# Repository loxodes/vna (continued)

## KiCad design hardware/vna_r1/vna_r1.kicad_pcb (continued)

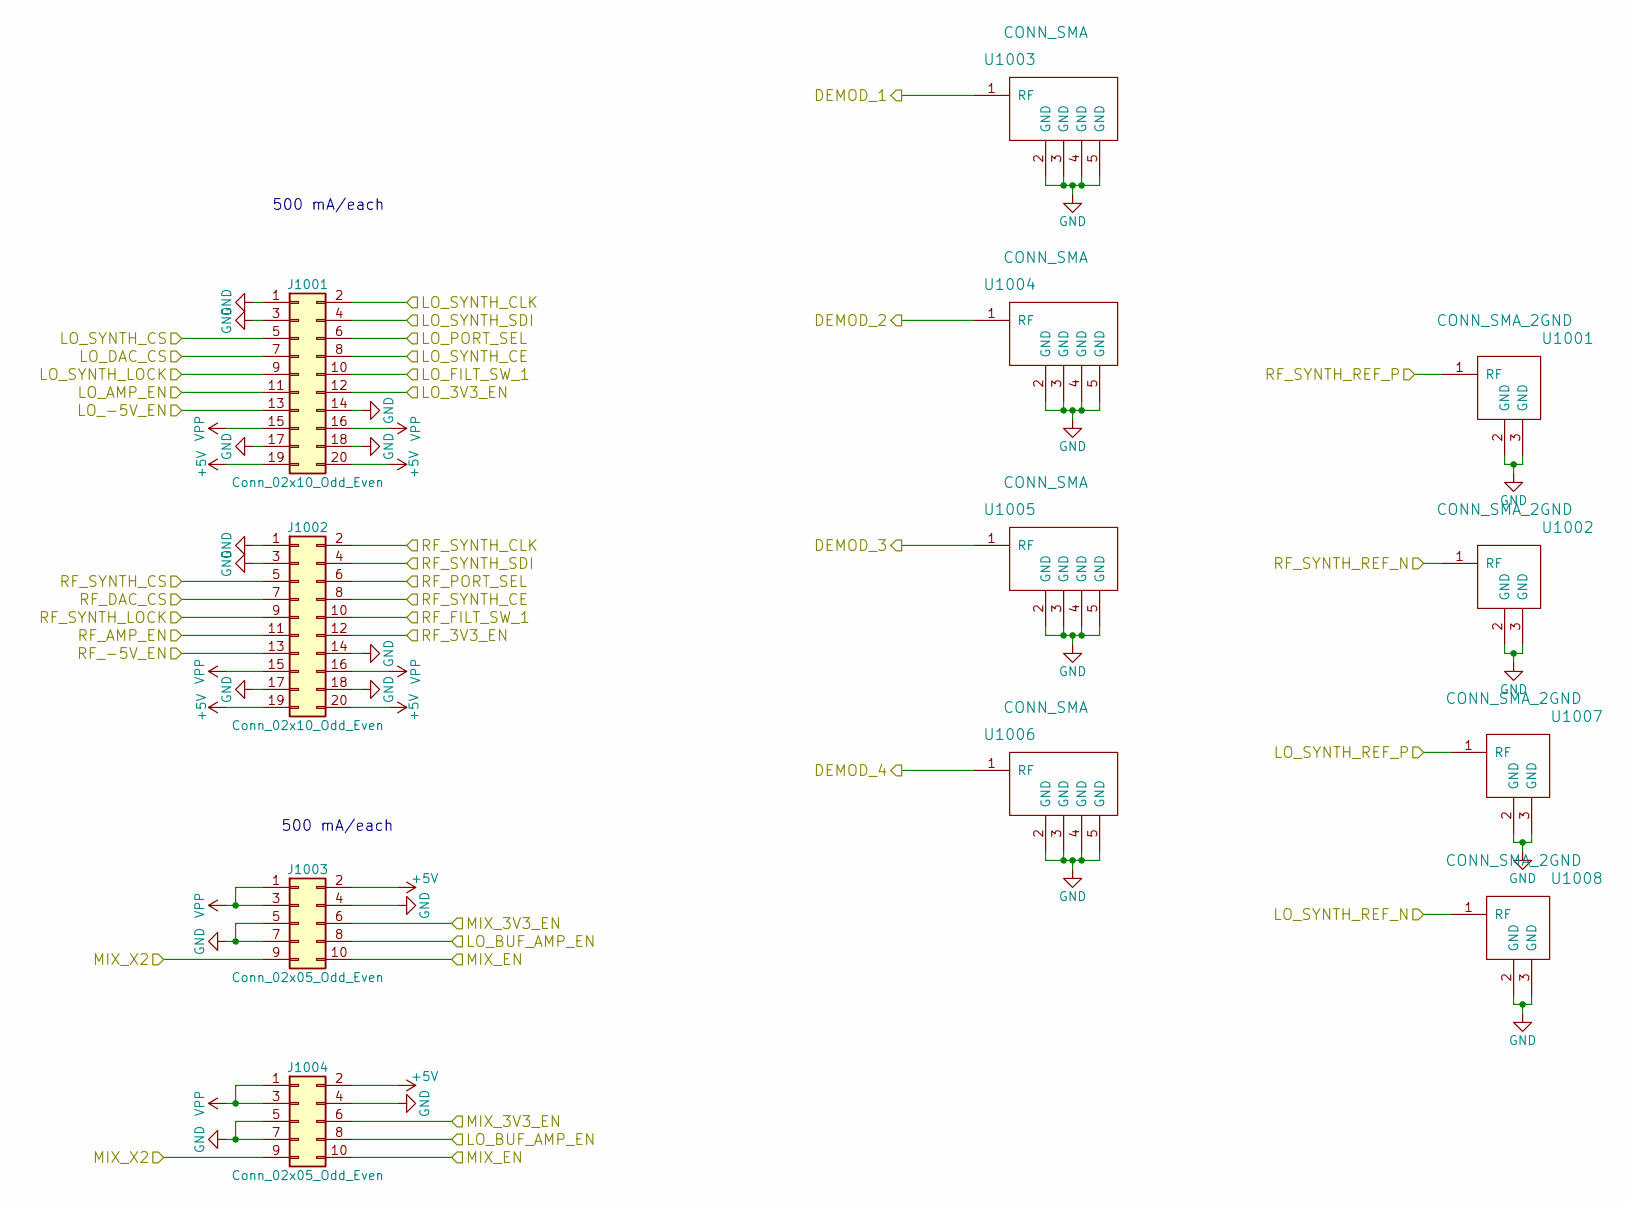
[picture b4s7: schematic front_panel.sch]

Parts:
J1001, J1002: Conn_02x10_Odd_Even; IDC_Header_Straight_20pins
J1003, J1004: Conn_02x05_Odd_Even; IDC_Header_Straight_10pins
U1001, U1002, U1007, U1008: CONN_SMA_2GND; 734120110_ufl_umc
U1003, U1004, U1005, U1006: CONN_SMA; 732511150_sma_thin

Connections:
+5V: J1001.19, J1001.20, J1002.19, J1002.20, J1003.2, J1004.2; also elsewhere on the board
/3V3_DEMOD_EXT_EN: J1003.6, J1004.6; also elsewhere on the board
/LO_3V3_EN: J1001.12; also elsewhere on the board
/LO_-5V_EN: J1001.13; also elsewhere on the board
/LO_AMP_EN: J1001.11; also elsewhere on the board
/LO_BUF_AMP_EN: J1003.8, J1004.8; also elsewhere on the board
/LO_DAC_CS: J1001.7; also elsewhere on the board
/LO_PORT_SEL: J1001.6; also elsewhere on the board
/LO_SPI_CLK: J1001.2; also elsewhere on the board
/LO_SPI_SDI: J1001.4; also elsewhere on the board
/LO_SYNTH_CE: J1001.8; also elsewhere on the board
/LO_SYNTH_CS: J1001.5; also elsewhere on the board
/LO_SYNTH_LOCK: J1001.9; also elsewhere on the board
/MIX_EN: J1003.10, J1004.10; also elsewhere on the board
/MIX_X2: J1003.9, J1004.9; also elsewhere on the board
/RF_3V3_EN: J1002.12; also elsewhere on the board
/RF_-5V_EN: J1002.13; also elsewhere on the board
/RF_AMP_EN: J1002.11; also elsewhere on the board
/RF_DAC_CS: J1002.7; also elsewhere on the board
/RF_FILT_SW_1: J1002.10; also elsewhere on the board
/RF_FILT_SW_2: J1001.10; also elsewhere on the board
/RF_PORT_SEL: J1002.6; also elsewhere on the board
/RF_SPI_CLK: J1002.2; also elsewhere on the board
/RF_SPI_SDI: J1002.4; also elsewhere on the board
/RF_SYNTH_CE: J1002.8; also elsewhere on the board
/RF_SYNTH_CS: J1002.5; also elsewhere on the board
/RF_SYNTH_LOCK: J1002.9; also elsewhere on the board
/SYNTH_REF_AN: U1008.1 (RF); also elsewhere on the board
/SYNTH_REF_AP: U1007.1 (RF); also elsewhere on the board
/SYNTH_REF_BN: U1002.1 (RF); also elsewhere on the board
/SYNTH_REF_BP: U1001.1 (RF); also elsewhere on the board
/front_panel/DEMOD_1: U1003.1 (RF); also elsewhere on the board
/front_panel/DEMOD_2: U1004.1 (RF); also elsewhere on the board
/front_panel/DEMOD_3: U1005.1 (RF); also elsewhere on the board
/front_panel/DEMOD_4: U1006.1 (RF); also elsewhere on the board
GND: J1001.1, J1001.3, J1001.14, J1001.17, J1001.18, J1002.1, J1002.3, J1002.14, J1002.17, J1002.18, J1003.4, J1003.5, J1003.7, J1004.4, J1004.5, J1004.7, U1001.2 (GND), U1001.3 (GND), U1002.2 (GND), U1002.3 (GND), U1003.2 (GND), U1003.3 (GND), U1003.4 (GND), U1003.5 (GND), U1004.2 (GND), U1004.3 (GND), U1004.4 (GND), U1004.5 (GND), U1005.2 (GND), U1005.3 (GND), U1005.4 (GND), U1005.5 (GND), U1006.2 (GND), U1006.3 (GND), U1006.4 (GND), U1006.5 (GND), U1007.2 (GND), U1007.3 (GND), U1008.2 (GND), U1008.3 (GND); also elsewhere on the board
VPP: J1001.15, J1001.16, J1002.15, J1002.16, J1003.1, J1003.3, J1004.1, J1004.3; also elsewhere on the board

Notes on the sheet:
500 mA/each

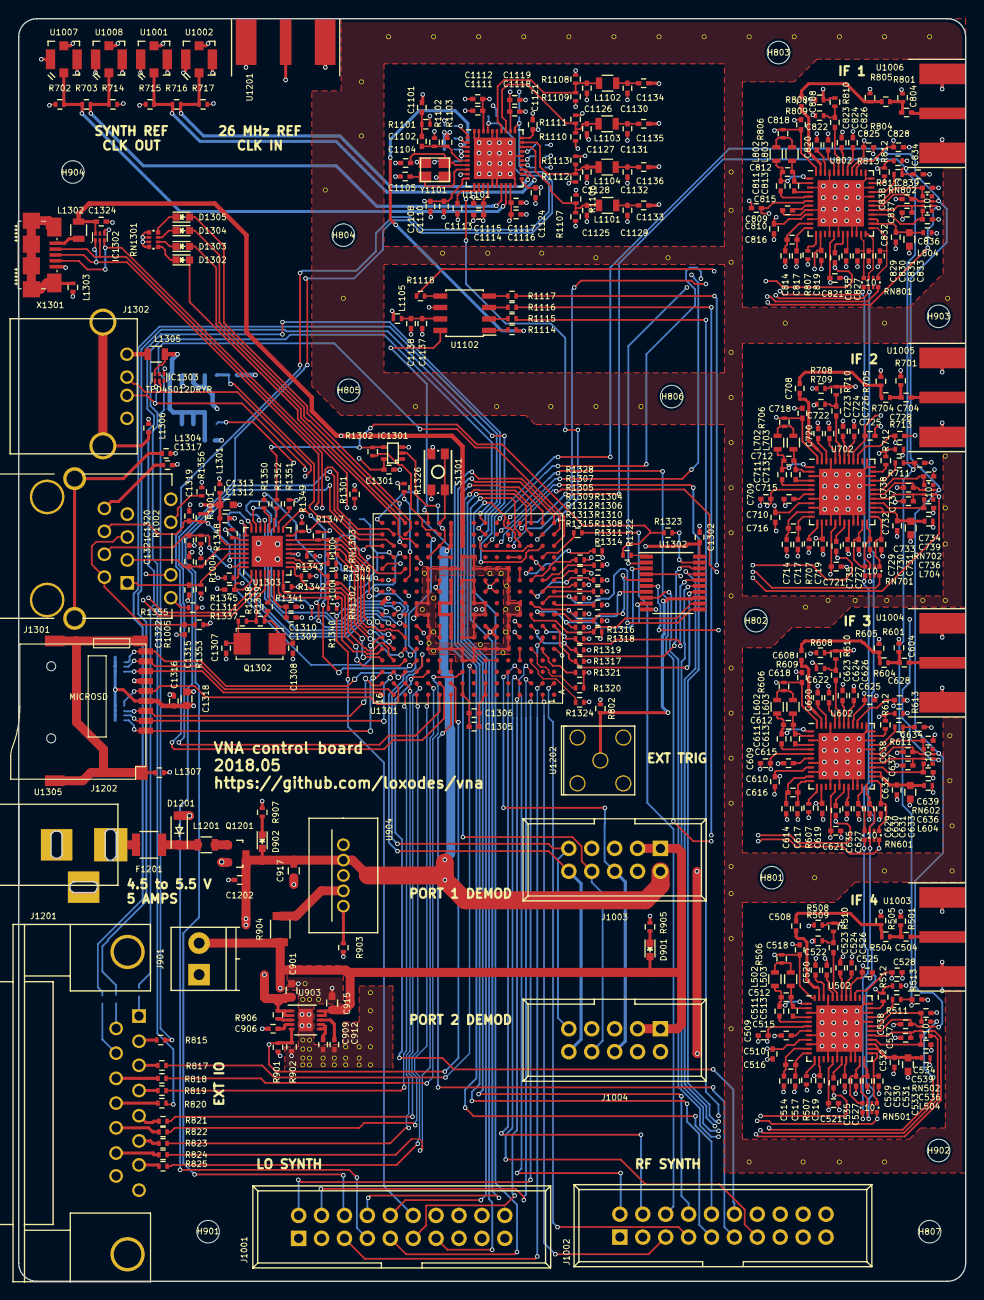
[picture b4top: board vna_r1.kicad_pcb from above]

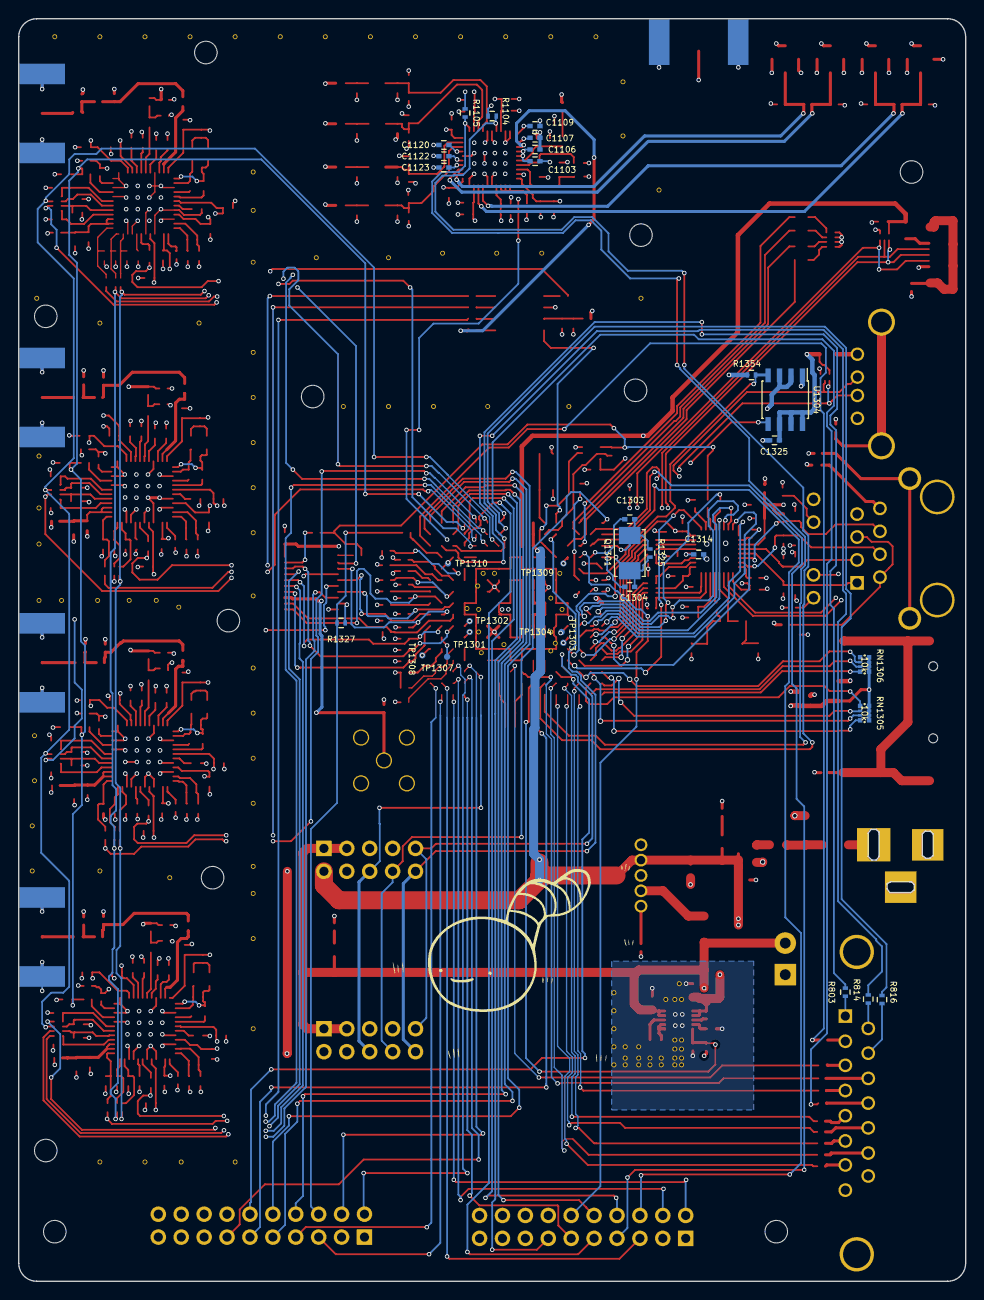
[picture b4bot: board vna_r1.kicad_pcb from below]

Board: 4 copper layers, 105.0 x 140.0 mm, 447 parts (31 on the bottom side), 375 nets.

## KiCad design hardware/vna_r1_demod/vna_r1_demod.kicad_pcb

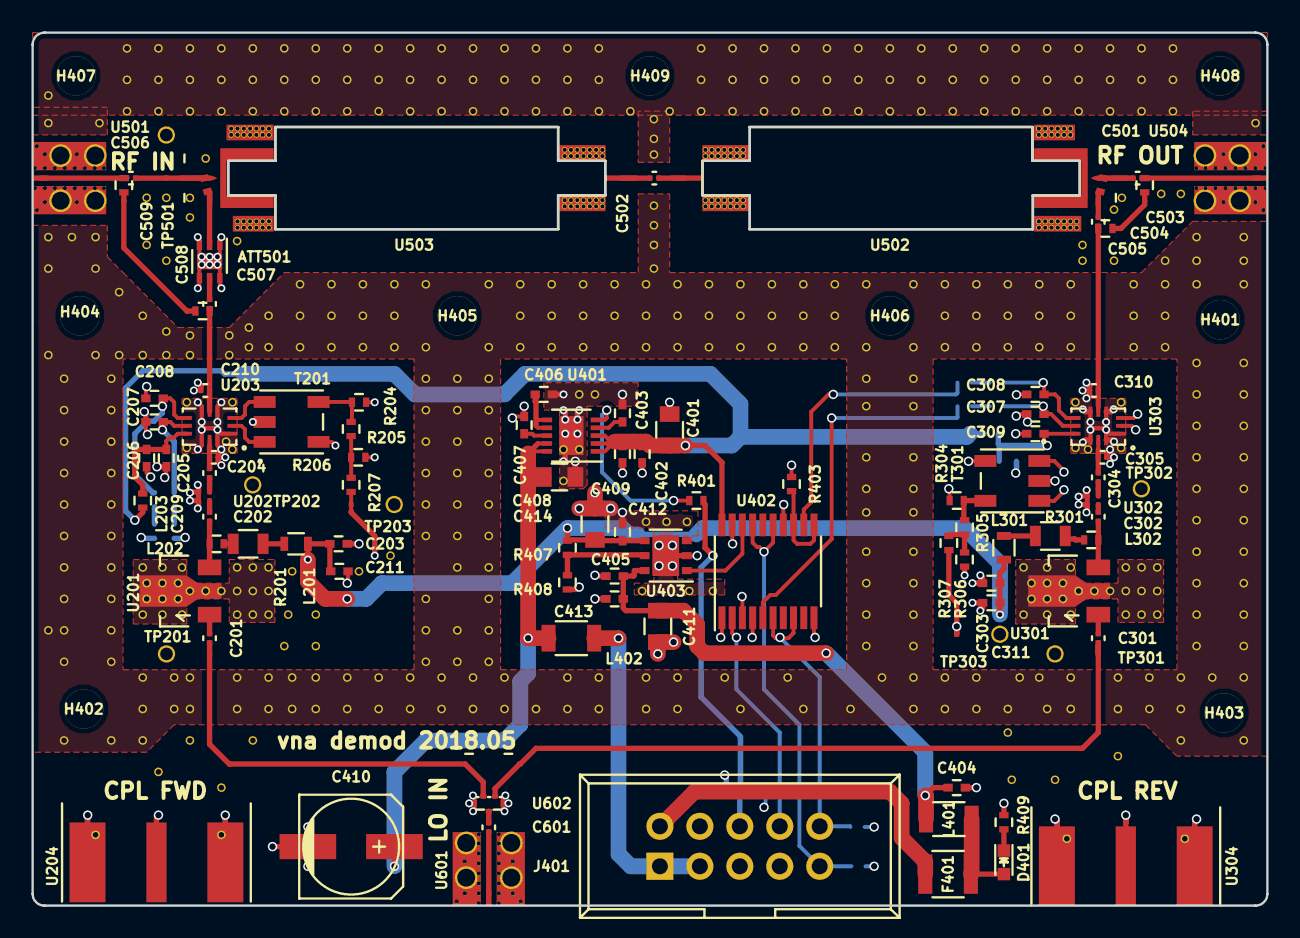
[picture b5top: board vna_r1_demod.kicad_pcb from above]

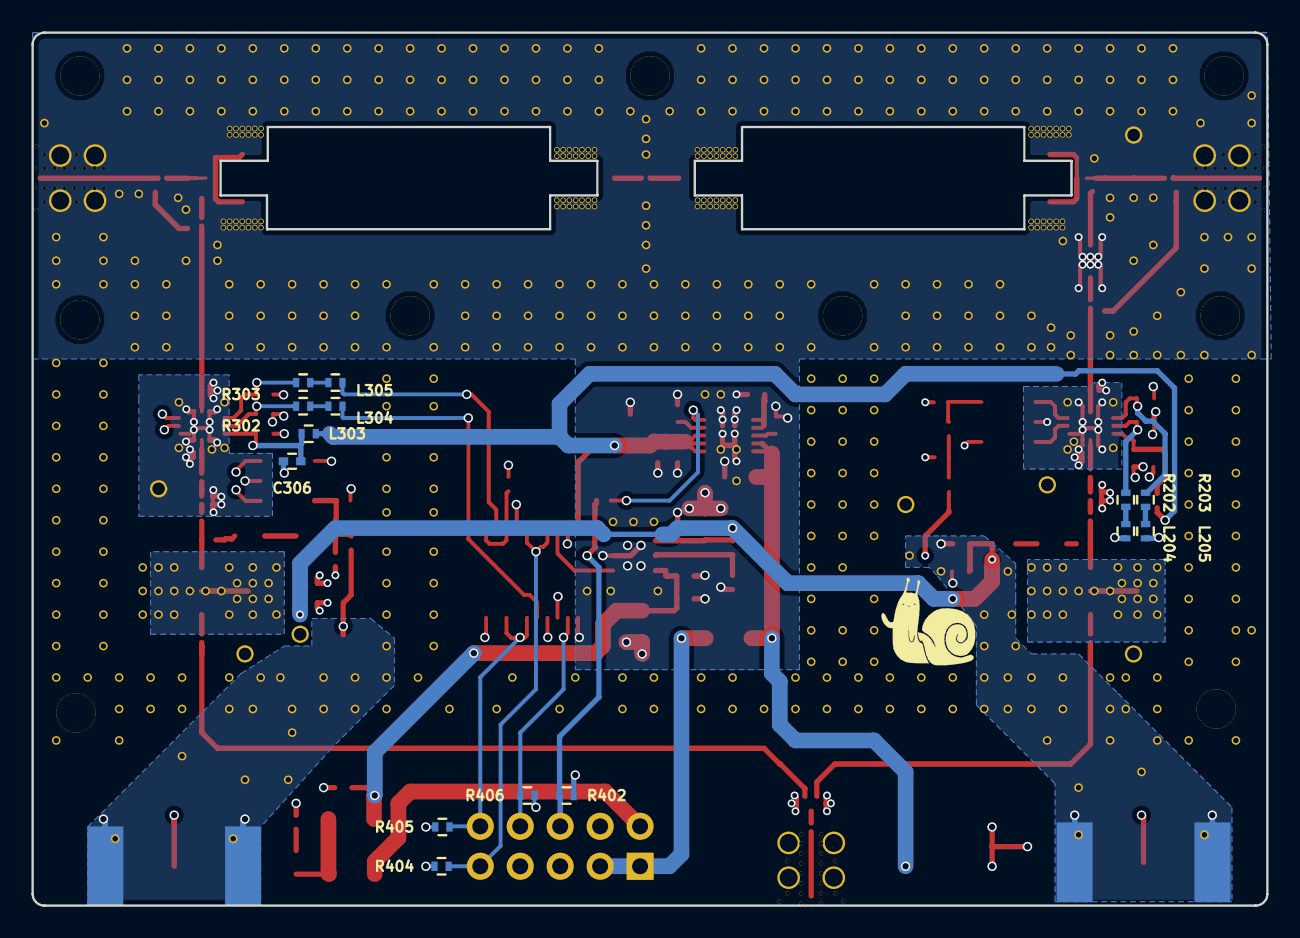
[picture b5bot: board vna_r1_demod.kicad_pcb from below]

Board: 4 copper layers, 78.5 x 55.5 mm, 120 parts (14 on the bottom side), 75 nets.

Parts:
ATT501: HMC657LP2E; DFN-6-1EP_2x2mm_Pitch0.65mm
C201, C202, C204, C205, C301, C302, C304, C305, C505, C507, C601: C_Small; C_0201
C203, C206, C207, C208, C209, C211, C303, C306, C307, C308, C309, C311, C409: C_Small; C_0402
C210, C310: DNP; C_0201
C401, C408: 10 uF; C_0805
C402, C403, C404, C406, C407, C413: 1 uF; C_0402
C405, C412: 100 nF; C_0402
C410: 4.7 uF; c_elec_6.3x5.8
C411, C414: 4.7 uF; C_0805
C501, C502, C506: 10 pF; C_0201
C503, C504, C508, C509: DNP; R_0402
D401: LED; LED_0603
F401: Polyfuse_Small; R_1210
H401, H402, H403, H404, H405, H406, H407, H408, H409: MOUNTING_HOLE; MountingHole_2-5mm
J401: Conn_02x05_Odd_Even; IDC_Header_Straight_10pins
L201, L301: L_Small; R_0603
L202, L203, L204, L205, L302, L303, L304, L305: L_Small; R_0402
L401, L402: L_Small; R_1206
R201, R301: 13; R_0805
R202, R203, R204, R205, R206, R207, R302, R303, R304, R305, R306, R307: R_Small; R_0402
R401: 100; R_0402
R402, R403, R404, R405, R406, R409: 10k; R_0402
R407: 47k; R_0402
R408: 12k; R_0402
T201, T301: Transformer_SP_1S; 5LEAD_BALUN_4p83mm_3p3mm
TP201, TP202, TP203, TP301, TP302, TP303, TP501: TP_RF; TP-P20B
U201, U301: SKY65013-70LF; SOT89-3_Housing
U202, U302: PAT0510S-C-XDB-T10; PAT0510S
U203, U303: LTC5548; QFN_12_3mm2mm
U204, U304: CONN_SMA; 732511150_sma_thin
U401: ADP7158; DFN-10-1EP_3x3mm_Pitch0.5mm
U402: 74HC244; TSSOP-20_4.4x6.5mm_Pitch0.65mm
U403: LD39100; DFN-6-1EP_3x3mm_Pitch0.95mm
U501, U504, U601: CONN_SMA_2GND; SMA_901-10512_6p7MIL_FR408_CPW_LAUNCH
U502: resistive_bridge; resistive_bridge_osh_fr408_ustrip_mirrored
U503: resistive_bridge; resistive_bridge_osh_fr408_ustrip
U602: PWR_SPLITTER; PS1608

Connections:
+3V3: C401.1, C402.1, C409.1, L203.2, L303.2, U401.1, U401.2, U401.3, U402.20
+5V: C404.1, C405.1, C411.1, C413.1, L401.2, U403.6
/LO_AMP_A: C203.2, C211.2, C303.2, C311.2, C412.1, C414.1, L201.2, L301.2, R407.1, U403.4
/MIX_EN_A: L205.2, U402.14
/MIX_EN_B: L305.2, U402.12
/X2_EN_A: L204.2, U402.3
/X2_EN_B: L304.2, U402.5
/couplers/CPL_FWD: C210.2, C507.1, C508.2, U203.5
/couplers/CPL_REV: C310.2, C504.2, C505.1, U303.5
/lo_split/LO_A: C201.2, TP201.1, U602.3
/lo_split/LO_B: C301.2, TP301.1, U602.2
/power_conn/EXT_3V3_EN: J401.6, R401.2, R402.2
/power_conn/EXT_LO_AMP_EN: J401.8, R406.2, U402.2
/power_conn/EXT_MIX_EN: J401.10, R405.2, U402.6, U402.8
/power_conn/EXT_X2_EN: J401.9, R404.2, U402.15, U402.17
/power_conn/LO_AMP_EN: U402.18, U403.1
GND: ATT501.1, ATT501.3, ATT501.4, ATT501.6, ATT501.7, C203.1, C205.2, C206.2, C207.1, C208.1, C209.2, C210.1, C211.1, C303.1, C305.2, C306.2, C307.1, C308.1, C309.2, C310.1, C311.1, C401.2, C402.2, C403.2, C404.2, C405.2, C406.2, C407.2, C408.2, C409.2, C410.2, C411.2, C412.2, C413.2, C414.2, J401.4, J401.5, J401.7, R204.2, R206.2, R304.2, R306.2, R402.1, R403.1, R404.1, R405.1, R406.1, R408.2, R409.1, T201.2, T201.5, T301.2, T301.5, TP201.2, TP202.2, TP203.2, TP301.2, TP302.2, TP303.2, TP501.2, U201.2, U202.3, U202.4, U203.1, U203.4, U203.6, U203.10, U203.12, U203.13, U204.2, U204.3, U204.4, U204.5, U301.2, U302.3, U302.4, U303.1, U303.4, U303.6, U303.10, U303.12, U303.13, U304.2, U304.3, U304.4, U304.5, U401.11, U402.1, U402.4, U402.10, U402.19, U403.2, U403.7, U501.2, U501.3, U502.4, U503.4, U504.2, U504.3, U601.2, U601.3, U602.4
unnamed: ATT501.2, U503.3
unnamed: ATT501.5, C507.2
unnamed: C201.1, U201.1
unnamed: C202.1, U202.2
unnamed: C202.2, L202.1, U201.3
unnamed: C204.1, TP202.1, U202.1
unnamed: C204.2, C205.1, U203.11
unnamed: C206.1, C209.1, L203.1, U203.9
unnamed: C207.2, R202.1, U203.8
unnamed: C208.2, R203.1, U203.7
unnamed: C301.1, U301.1
unnamed: C302.1, U302.2
unnamed: C302.2, L302.1, U301.3
unnamed: C304.1, TP302.1, U302.1
unnamed: C304.2, C305.1, U303.11
unnamed: C306.1, C309.1, L303.1, U303.9
unnamed: C307.2, R302.1, U303.8
unnamed: C308.2, R303.1, U303.7
unnamed: C403.1, U401.4
unnamed: C406.1, U401.6, U401.7
unnamed: C407.1, U401.8
unnamed: C501.1, U502.2
unnamed: C501.2, C503.2, U504.1
unnamed: C502.1, U503.1
unnamed: C502.2, U502.1
unnamed: C503.1, C504.1
unnamed: C505.2, U502.3
unnamed: C506.1, C509.2, U501.1
unnamed: C506.2, TP501.1, U503.2
unnamed: C508.1, C509.1
unnamed: C601.1, U602.1
unnamed: C601.2, U601.1
unnamed: D401.1, R409.2
unnamed: D401.2, F401.1, L401.1
unnamed: F401.2, J401.2
unnamed: J401.1, J401.3, L402.2
unnamed: L201.1, R201.2
unnamed: L202.2, R201.1
unnamed: L204.1, R202.2
unnamed: L205.1, R203.2
unnamed: L301.1, R301.2
unnamed: L302.2, R301.1
unnamed: L304.1, R302.2
unnamed: L305.1, R303.2
unnamed: R204.1, R205.1, T201.4
unnamed: R205.2, R206.1, R207.1
unnamed: R207.2, TP203.1, U204.1
unnamed: R304.1, R305.1, T301.4
unnamed: R305.2, R306.1, R307.1
unnamed: R307.2, TP303.1, U304.1
unnamed: R401.1, U401.5
unnamed: R403.2, U402.11, U402.13
unnamed: R407.2, R408.1, U403.5
unnamed: T201.1, U203.2
unnamed: T201.3, U203.3
unnamed: T301.1, U303.2
unnamed: T301.3, U303.3
VPP: C408.1, C410.1, L402.1, U401.9, U401.10

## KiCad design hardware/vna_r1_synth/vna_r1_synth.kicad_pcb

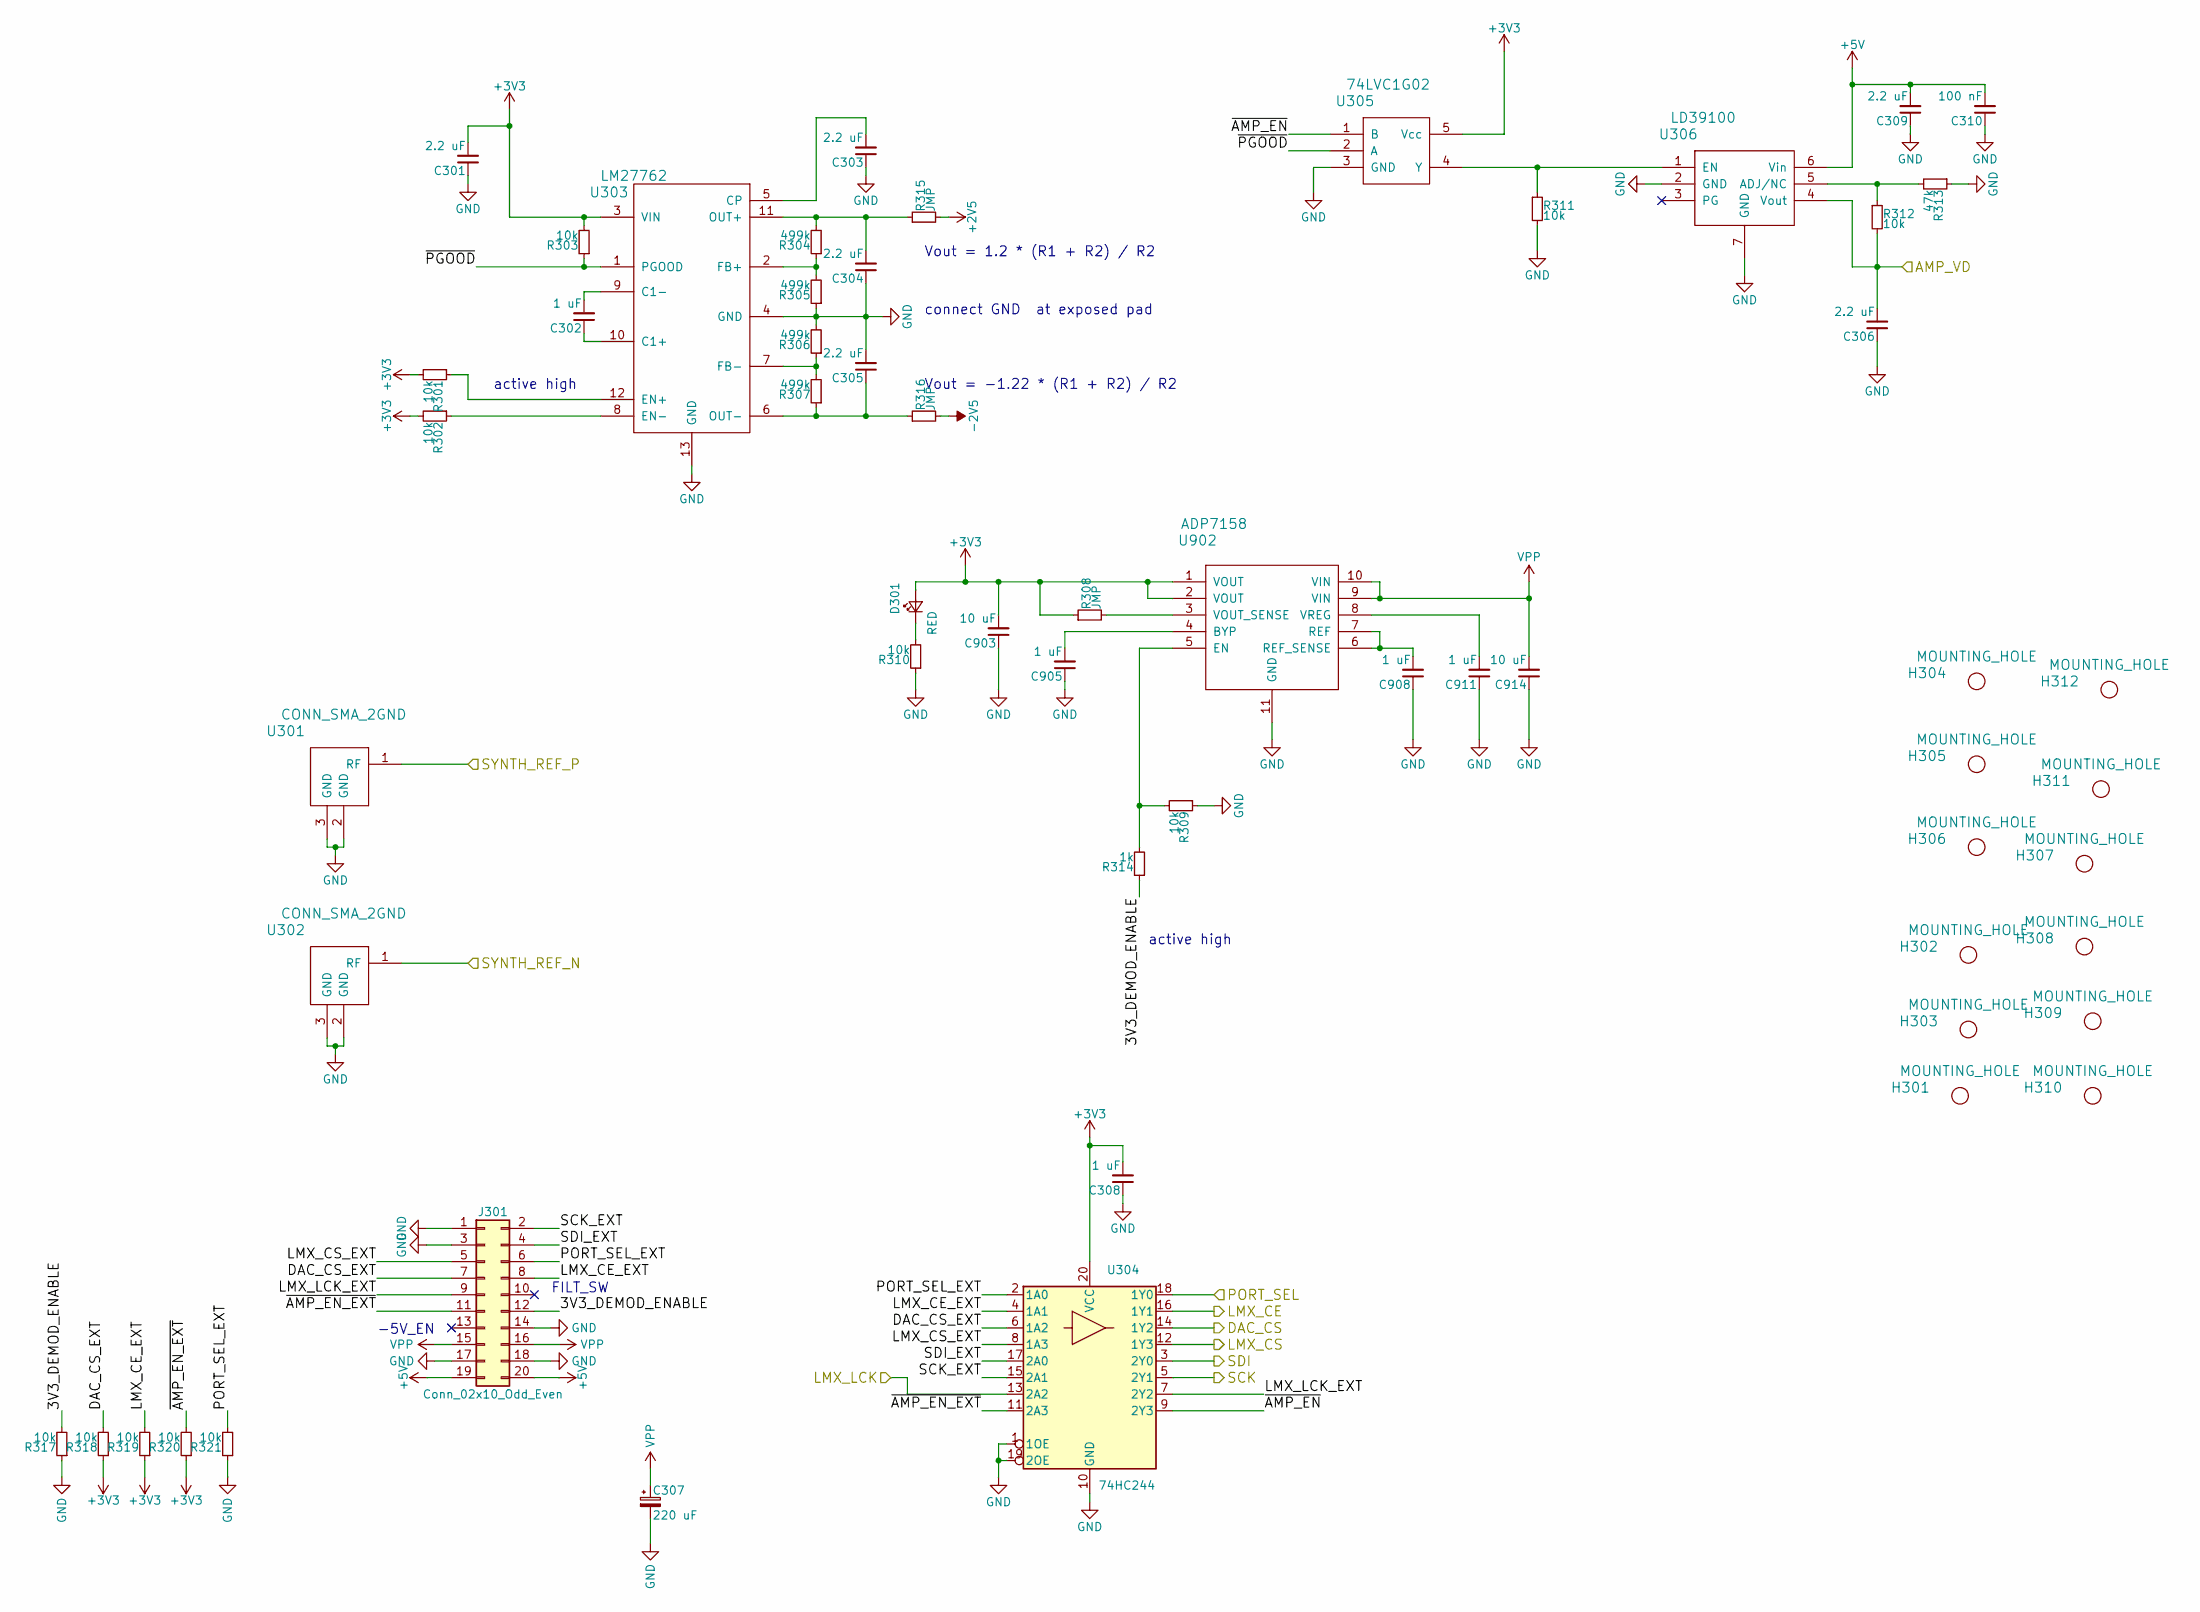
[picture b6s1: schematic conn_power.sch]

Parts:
C301, C303, C304, C305, C309: 2.2 uF; C_0603
C302, C308, C905, C908, C911: 1 uF; C_0402
C306: 2.2 uF; C_0402
C307: 220 uF; c_elec_6.3x5.8
C310: 100 nF; C_0402
C903, C914: 10 uF; C_0603
D301: RED; LED_0603
H301, H302, H303, H304, H305, H306, H307, H308, H309, H310, H311, H312: MOUNTING_HOLE; MountingHole_2-5mm
J301: Conn_02x10_Odd_Even; IDC_Header_Straight_20pins
R301, R302, R303, R309, R310, R311, R312, R317, R318, R319, R320, R321: 10k; R_0402
R304, R305, R306, R307: 499k; R_0402
R308, R315, R316: JMP; R_0402
R313: 47k; R_0402
R314: 1k; R_0402
U301, U302: CONN_SMA_2GND; 734120110_ufl_umc
U303: LM27762; WSON-12-1EP_3x2mm_Pitch0.5mm
U304: 74HC244; TSSOP-20_4.4x6.5mm_Pitch0.65mm
U305: 74LVC1G02; SOT-23-5
U306: LD39100; DFN-6-1EP_3x3mm_Pitch0.95mm
U902: ADP7158; DFN-10-1EP_3x3mm_Pitch0.5mm

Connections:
+2V5: R315.2; also elsewhere on the board
+3V3: C301.2, C308.2, C903.2, D301.2 (A), R301.2, R302.2, R303.2, R308.1, R318.1, R319.1, R320.1, U303.3 (VIN), U304.20 (VCC), U305.5 (Vcc), U902.1 (VOUT), U902.2 (VOUT); also elsewhere on the board
+5V: C309.2, C310.2, J301.19, J301.20, U306.6 (Vin)
-2V5: R316.2; also elsewhere on the board
/AMP_VD: C306.2, R312.2, U306.4 (Vout); also elsewhere on the board
/DAC_CS: U304.14 (1Y2); also elsewhere on the board
/PORT_SEL: U304.18 (1Y0); also elsewhere on the board
/SPI_SCK: U304.5 (2Y1); also elsewhere on the board
/SPI_SDI: U304.3 (2Y0); also elsewhere on the board
/conn_power/3V3_DEMOD_ENABLE: J301.12, R314.1, R317.2
/conn_power/DAC_CS_EXT: J301.7, R318.2, U304.6 (1A2)
/conn_power/LMX_CE: U304.16 (1Y1); also elsewhere on the board
/conn_power/LMX_CE_EXT: J301.8, R319.2, U304.4 (1A1)
/conn_power/LMX_CS: U304.12 (1Y3); also elsewhere on the board
/conn_power/LMX_CS_EXT: J301.5, U304.8 (1A3)
/conn_power/LMX_LCK: U304.13 (2A2); also elsewhere on the board
/conn_power/LMX_LCK_EXT: J301.9, U304.7 (2Y2)
/conn_power/PORT_SEL_EXT: J301.6, R321.2, U304.2 (1A0)
/conn_power/SCK_EXT: J301.2, U304.15 (2A1)
/conn_power/SDI_EXT: J301.4, U304.17 (2A0)
/conn_power/SYNTH_REF_N: U302.1 (RF); also elsewhere on the board
/conn_power/SYNTH_REF_P: U301.1 (RF); also elsewhere on the board
/conn_power/~AMP_EN: U304.9 (2Y3), U305.1 (B)
/conn_power/~AMP_EN_EXT: J301.11, R320.2, U304.11 (2A3)
/conn_power/~PGOOD: R303.1, U303.1 (PGOOD), U305.2 (A)
GND: C301.1, C303.1, C304.1, C305.2, C306.1, C307.2, C308.1, C309.1, C310.1, C903.1, C905.1, C908.1, C911.1, C914.1, J301.1, J301.3, J301.14, J301.17, J301.18, R305.1, R306.2, R309.1, R310.1, R311.2, R313.1, R317.1, R321.1, U301.2 (GND), U301.3 (GND), U302.2 (GND), U302.3 (GND), U303.4 (GND), U303.13 (GND), U304.1 (1OE), U304.10 (GND), U304.19 (2OE), U305.3 (GND), U306.2 (GND), U306.7 (GND), U902.11 (GND); also elsewhere on the board
unnamed: C302.1, U303.10 (C1+)
unnamed: C302.2, U303.9 (C1-)
unnamed: C303.2, U303.5 (CP)
unnamed: C304.2, R304.2, R315.1, U303.11 (OUT+)
unnamed: C305.1, R307.1, R316.1, U303.6 (OUT-)
unnamed: C905.2, U902.4 (BYP)
unnamed: C908.2, U902.6 (REF_SENSE), U902.7 (REF)
unnamed: C911.2, U902.8 (VREG)
unnamed: D301.1 (K), R310.2
unnamed: R301.1, U303.12 (EN+)
unnamed: R302.1, U303.8 (EN-)
unnamed: R304.1, R305.2, U303.2 (FB+)
unnamed: R306.1, R307.2, U303.7 (FB-)
unnamed: R308.2, U902.3 (VOUT_SENSE)
unnamed: R309.2, R314.2, U902.5 (EN)
unnamed: R311.1, U305.4 (Y), U306.1 (EN)
unnamed: R312.1, R313.2, U306.5 (ADJ/NC)
VPP: C307.1, C914.2, J301.15, J301.16, U902.9 (VIN), U902.10 (VIN)

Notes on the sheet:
active high
Vout = 1.2 * (R1 + R2) / R2
Vout = -1.22 * (R1 + R2) / R2
connect GND at exposed pad
-5V_EN
FILT_SW

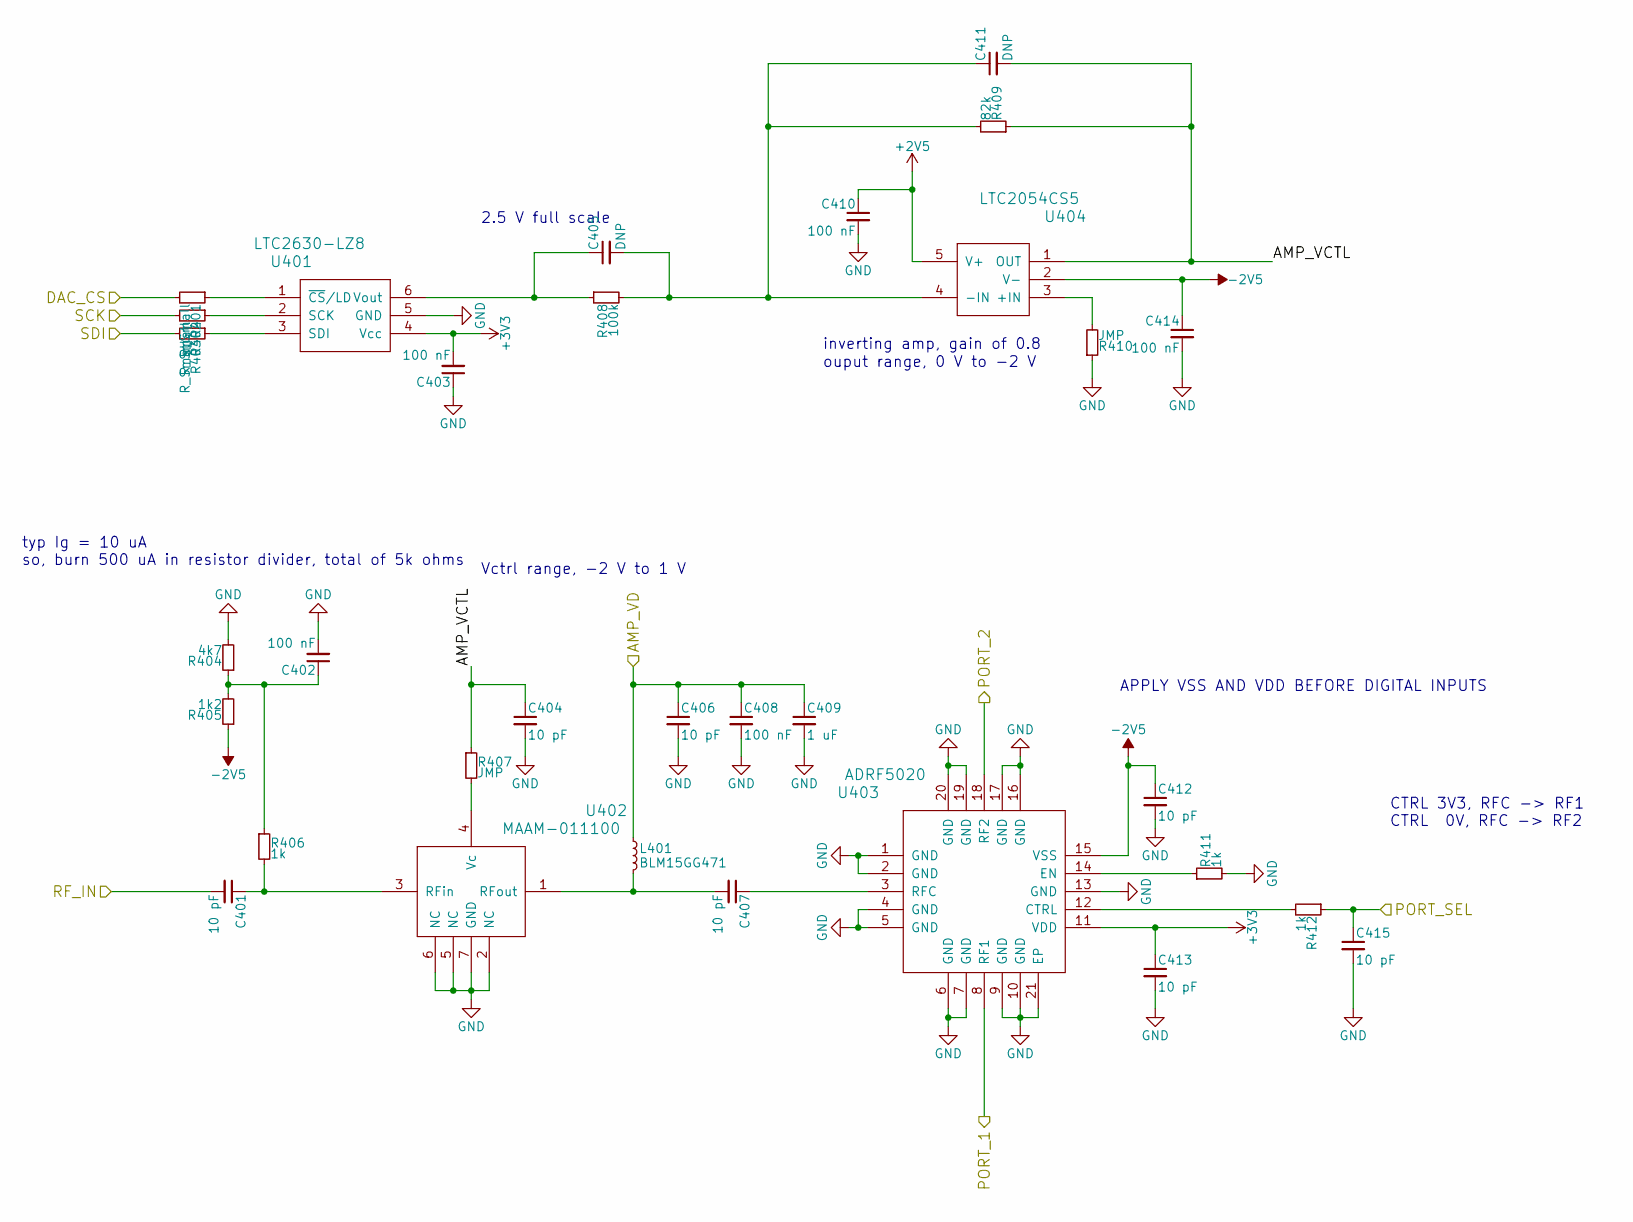
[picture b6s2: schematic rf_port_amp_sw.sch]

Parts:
C401, C407: 10 pF; C_0201
C402, C403, C408, C410, C414: 100 nF; C_0402
C404, C406, C412, C413, C415: 10 pF; C_0402
C405, C411: DNP; C_0402
C409: 1 uF; C_0402
L401: BLM15GG471; R_0402
R401, R402, R403: R_Small; R_0402
R404: 4k7; R_0402
R405: 1k2; R_0402
R406, R411, R412: 1k; R_0402
R407, R410: JMP; R_0402
R408: 100k; R_0402
R409: 82k; R_0402
U401: LTC2630-LZ8; SC-70-6
U402: MAAM-011100; TDFN6
U403: ADRF5020; ADRF5020BCCZN
U404: LTC2054CS5; SOT-23-5

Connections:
+2V5: C410.1, U404.5 (V+); also elsewhere on the board
+3V3: C403.2, C413.1, U401.4 (Vcc), U403.11 (VDD); also elsewhere on the board
-2V5: C412.1, C414.1, R405.1, U403.15 (VSS), U404.2 (V-); also elsewhere on the board
/AMP_VD: C406.1, C408.1, C409.1, L401.1; also elsewhere on the board
/DAC_CS: R401.2; also elsewhere on the board
/PORT_SEL: C415.1, R412.1; also elsewhere on the board
/RF_PORT: C401.2; also elsewhere on the board
/SPI_SCK: R402.2; also elsewhere on the board
/SPI_SDI: R403.2; also elsewhere on the board
/conn_front/PORT_1: U403.8 (RF1); also elsewhere on the board
/conn_front/PORT_2: U403.18 (RF2); also elsewhere on the board
/rf_port_amp_sw/AMP_VCTL: C404.1, C411.2, R407.1, R409.1, U404.1 (OUT)
GND: C402.2, C403.1, C404.2, C406.2, C408.2, C409.2, C410.2, C412.2, C413.2, C414.2, C415.2, R404.2, R410.1, R411.2, U401.5 (GND), U402.2 (NC), U402.5 (NC), U402.6 (NC), U402.7 (GND), U403.1 (GND), U403.2 (GND), U403.4 (GND), U403.5 (GND), U403.6 (GND), U403.7 (GND), U403.9 (GND), U403.10 (GND), U403.13 (GND), U403.16 (GND), U403.17 (GND), U403.19 (GND), U403.20 (GND), U403.21 (EP); also elsewhere on the board
unnamed: C401.1, R406.2, U402.3 (RFin)
unnamed: C402.1, R404.1, R405.2, R406.1
unnamed: C405.1, R408.1, U401.6 (Vout)
unnamed: C405.2, C411.1, R408.2, R409.2, U404.4 (-IN)
unnamed: C407.1, U403.3 (RFC)
unnamed: C407.2, L401.2, U402.1 (RFout)
unnamed: R401.1, U401.1 (~CS~/LD)
unnamed: R402.1, U401.2 (SCK)
unnamed: R403.1, U401.3 (SDI)
unnamed: R407.2, U402.4 (Vc)
unnamed: R410.2, U404.3 (+IN)
unnamed: R411.1, U403.14 (EN)
unnamed: R412.2, U403.12 (CTRL)

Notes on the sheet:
CTRL 3V3, RFC -> RF1 CTRL 0V, RFC -> RF2
APPLY VSS AND VDD BEFORE DIGITAL INPUTS
typ Ig = 10 uA so, burn 500 uA in resistor divider, total of 5k ohms
Vctrl range, -2 V to 1 V
2.5 V full scale
inverting amp, gain of 0.8
ouput range, 0 V to -2 V

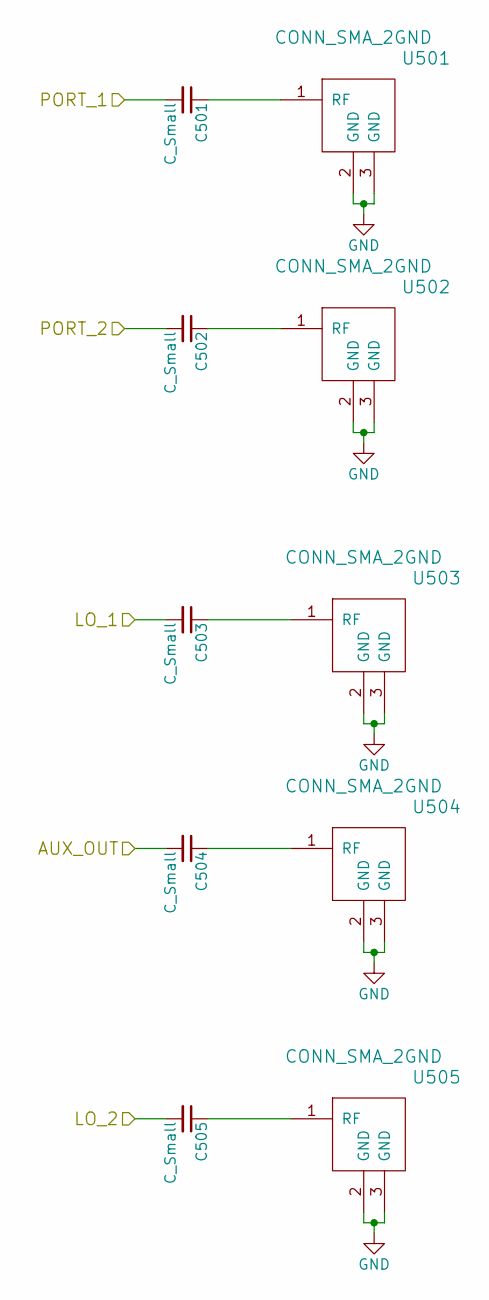
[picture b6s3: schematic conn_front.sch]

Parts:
C501, C502, C503, C504, C505: C_Small; C_0201
U501, U502, U503, U504, U505: CONN_SMA_2GND; SMA_901-10512_6p7MIL_FR408_CPW_LAUNCH

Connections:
/AUX_OUT: C504.2; also elsewhere on the board
/LO_PORT1: C503.2; also elsewhere on the board
/LO_PORT2: C505.2; also elsewhere on the board
/conn_front/PORT_1: C501.2; also elsewhere on the board
/conn_front/PORT_2: C502.2; also elsewhere on the board
GND: U501.2 (GND), U501.3 (GND), U502.2 (GND), U502.3 (GND), U503.2 (GND), U503.3 (GND), U504.2 (GND), U504.3 (GND), U505.2 (GND), U505.3 (GND); also elsewhere on the board
unnamed: C501.1, U501.1 (RF)
unnamed: C502.1, U502.1 (RF)
unnamed: C503.1, U503.1 (RF)
unnamed: C504.1, U504.1 (RF)
unnamed: C505.1, U505.1 (RF)
